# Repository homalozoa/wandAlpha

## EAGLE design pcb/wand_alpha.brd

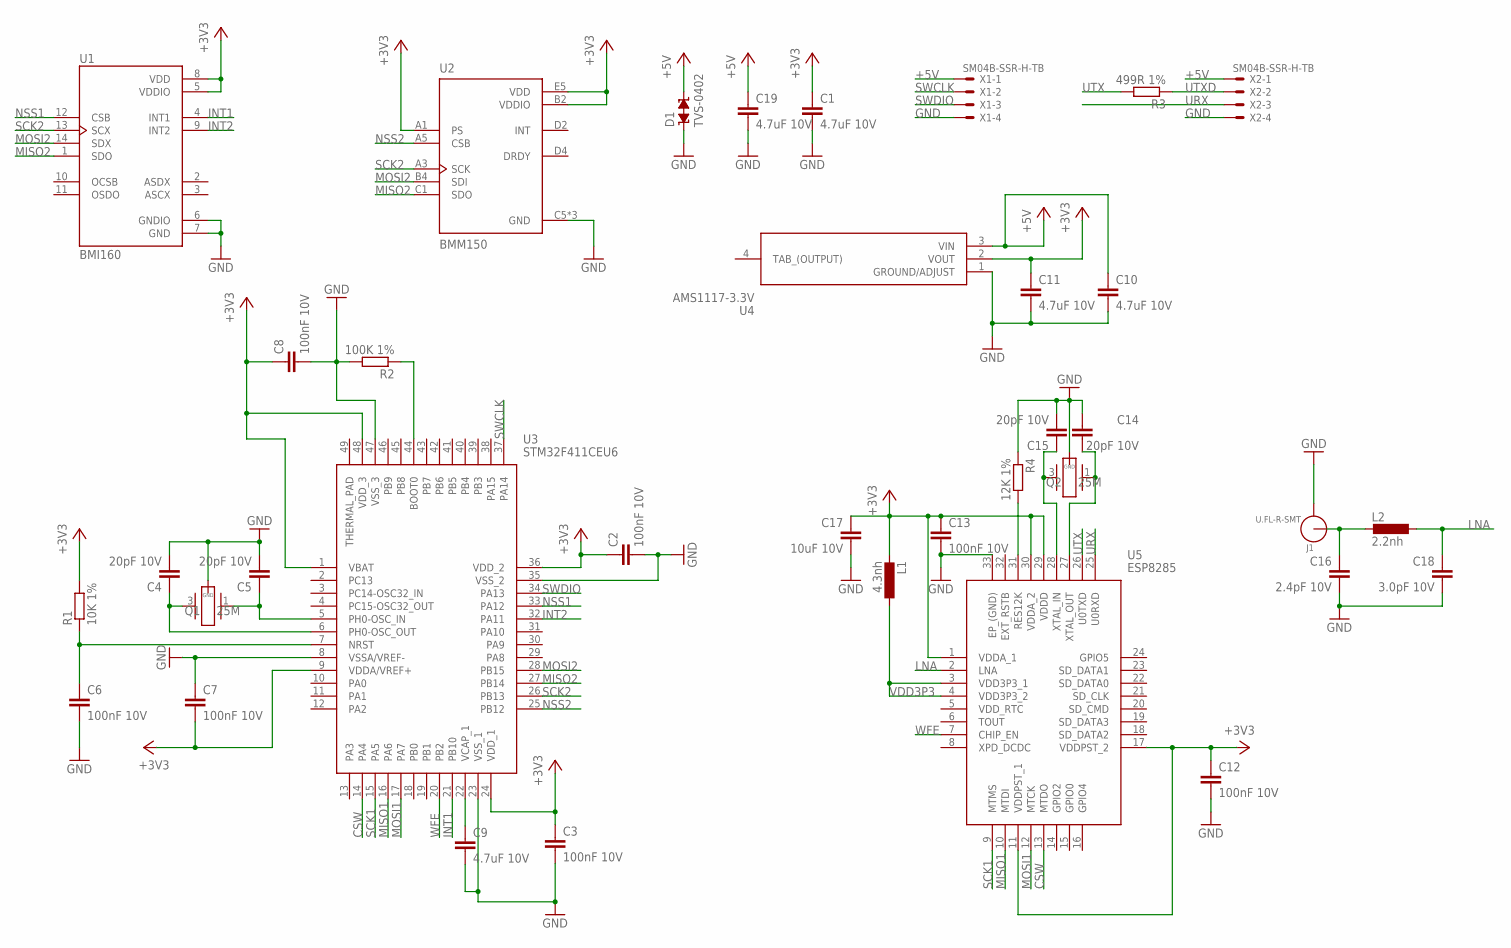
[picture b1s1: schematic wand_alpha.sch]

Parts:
C1, C9, C10, C11, C19: 4.7uF 10V; C0402
C2, C3, C6, C7, C8, C12, C13: 100nF 10V; C0402
C4, C5, C14, C15: 20pF 10V; C0402
C16: 2.4pF 10V; C0402
C17: 10uF 10V; C0402
C18: 3.0pF 10V; C0402
D1: TVS-0402; TVS0402
J1: U.FL-R-SMT; U.FL_SMT
L1: 4.3nh; L0402
L2: 2.2nh; L0402
Q1, Q2: 25M; FA-128
R1: 10K 1%; R0402
R2: 100K 1%; R0402
R3: 499R 1%; R0402
R4: 12K 1%; R0402
U1: BMI160; PQFN50P300X250X88-14N
U2: BMM150; XDCR_BMM150
U3: STM32F411CEU6; QFN50P700X700X60-49N
U4: AMS1117-3.3V; SOT229P700X180-4N
U5: ESP8285; QFN50P500X500X90-33N
X1, X2: SM04B-SSR-H-TB

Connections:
+3V3: C1.1, C2.1, C3.1, C7.2, C8.1, C11.1, C12.1, C13.1, C17.1, L1.2, R1.2, U1.5 (VDDIO), U1.8 (VDD), U2.A1 (PS), U2.B2 (VDDIO), U2.E5 (VDD), U3.1 (VBAT), U3.9 (VDDA/VREF+), U3.24 (VDD_1), U3.36 (VDD_2), U3.48 (VDD_3), U4.2 (VOUT), U5.1 (VDDA_1), U5.11 (VDDPST_1), U5.17 (VDDPST_2), U5.29 (VDDD), U5.30 (VDDA_2)
+5V: C10.1, C19.1, D1.2, U4.3 (VIN), X1.1, X2.1
CSW: U3.14 (PA4), U5.13 (MTDO)
GND: C1.2, C2.2, C3.2, C4.2, C5.2, C6.2, C7.1, C8.2, C9.2, C10.2, C11.2, C12.2, C13.2, C14.2, C15.2, C16.2, C17.2, C18.2, C19.2, D1.1, J1.GND1, J1.GND2, Q1.2 (GND), Q1.4 (GND), Q2.2 (GND), Q2.4 (GND), R2.2, R4.1, U1.6 (GNDIO), U1.7 (GND), U2.C5 (GND), U2.E1 (GND), U2.E3 (GND), U3.8 (VSSA/VREF-), U3.23 (VSS_1), U3.35 (VSS_2), U3.47 (VSS_3), U4.1 (GROUND/ADJUST), U5.33 (EP_(GND)), X1.4, X2.4
INT1: U1.4 (INT1), U3.21 (PB10)
INT2: U1.9 (INT2), U3.32 (PA11)
LNA: C18.1, L2.1, U5.2 (LNA)
MISO1: U3.16 (PA6), U5.10 (MTDI)
MISO2: U1.1 (SDO), U2.C1 (SDO), U3.27 (PB14)
MOSI1: U3.17 (PA7), U5.12 (MTCK)
MOSI2: U1.14 (SDX), U2.B4 (SDI), U3.28 (PB15)
unnamed: C4.1, Q1.3 (2), U3.6 (PH0-OSC_OUT)
unnamed: C5.1, Q1.1, U3.5 (PH0-OSC_IN)
unnamed: C6.1, R1.1, U3.7 (NRST)
unnamed: R2.1, U3.44 (BOOT0)
unnamed: C9.1, U3.22 (VCAP_1)
unnamed: C16.1, J1.SIG (ANT), L2.2
unnamed: C14.1, Q2.1, U5.27 (XTAL_OUT)
unnamed: C15.1, Q2.3 (2), U5.28 (XTAL_IN)
unnamed: R4.2, U5.31 (RES12K)
NSS1: U1.12 (CSB), U3.33 (PA12)
NSS2: U2.A5 (CSB), U3.25 (PB12)
SCK1: U3.15 (PA5), U5.9 (MTMS)
SCK2: U1.13 (SCX), U2.A3 (SCK), U3.26 (PB13)
SWCLK: U3.37 (PA14), X1.2
SWDIO: U3.34 (PA13), X1.3
URX: U5.25 (U0RXD), X2.3
UTX: R3.2, U5.26 (U0TXD)
UTXD: R3.1, X2.2
VDD3P3: L1.1, U5.3 (VDD3P3_1), U5.4 (VDD3P3_2)
WFE: U3.20 (PB2), U5.7 (CHIP_EN)

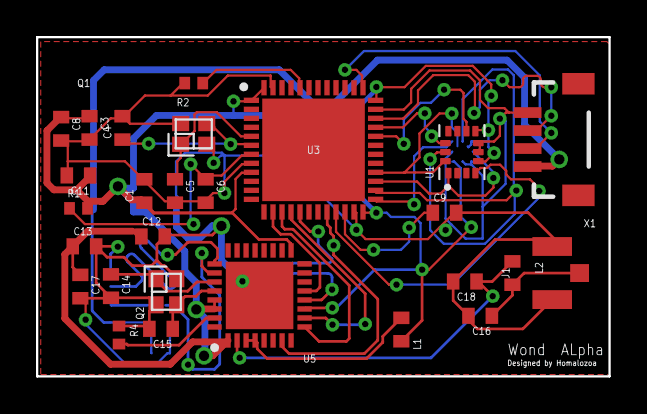
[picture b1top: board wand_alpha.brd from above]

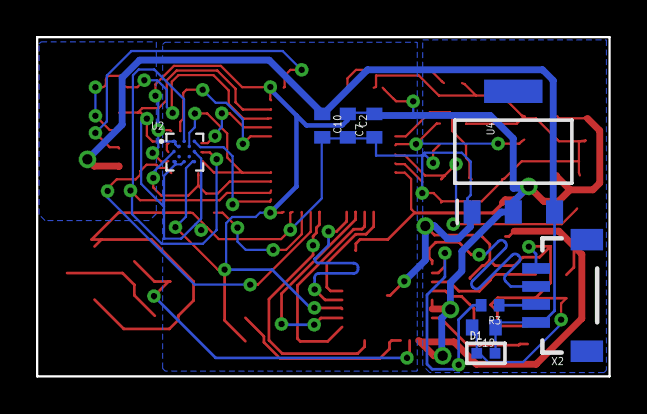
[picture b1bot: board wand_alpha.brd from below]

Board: 2 copper layers, 31.8 x 18.8 mm, 36 parts (9 on the bottom side), 31 nets.

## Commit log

2020-04-30 add pcb

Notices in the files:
parts and their libraries:
supressor: Copyright (C) 2009, Bob Starr
